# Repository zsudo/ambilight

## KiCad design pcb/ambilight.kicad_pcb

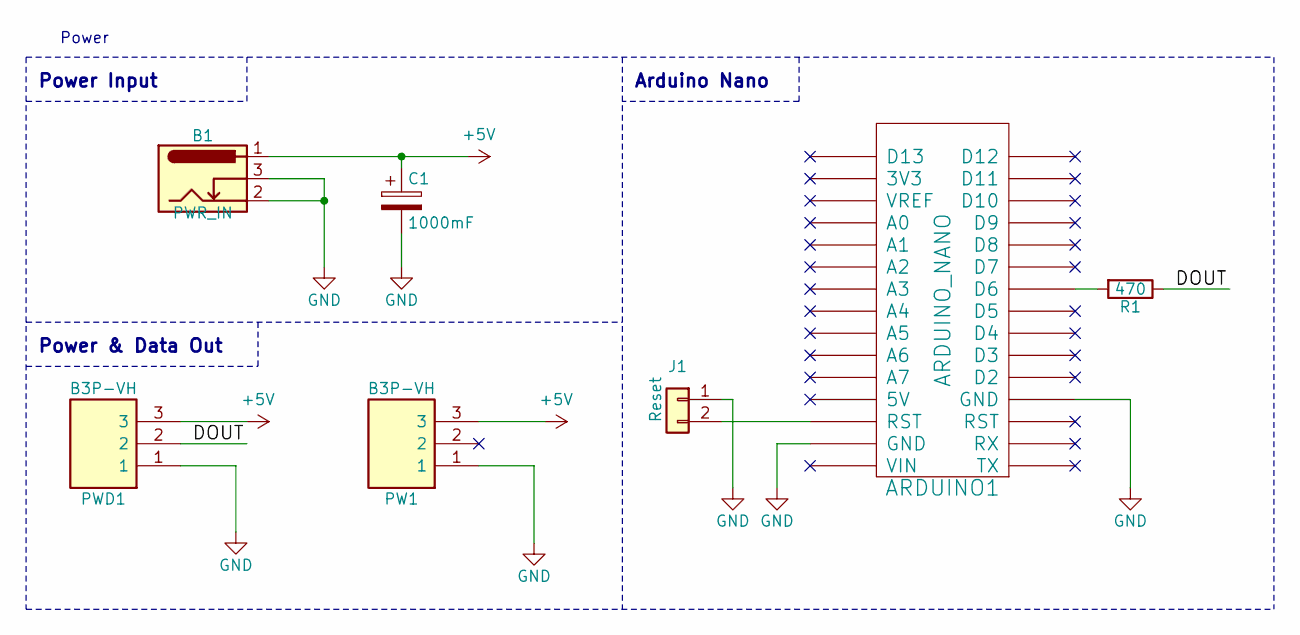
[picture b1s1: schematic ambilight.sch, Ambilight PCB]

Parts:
ARDUINO1: ARDUINO_NANO; Arduino_Nano
B1: PWR_IN; BarrelJack_Horizontal
C1: 1000mF; CP_Radial_D10.0mm_P5.00mm
J1: Reset; PinHeader_1x02_P2.54mm_Vertical
PW1: B3P-VH; SHDR3W114P0X396_1X3_1182X850X940P; Manufacturer_Part_Number B3P-VH
PWD1: B3P-VH; SHDR3W114P0X396_1X3_1182X850X940P; Manufacturer_Part_Number B3P-VH
R1: 470; R_Axial_DIN0411_L9.9mm_D3.6mm_P15.24mm_Horizontal

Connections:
+5V: B1.1, C1.1, PW1.3, PWD1.3
/DOUT: PWD1.2, R1.1
GND: ARDUINO1.4 (GND), ARDUINO1.29 (GND), B1.2, B1.3, C1.2, J1.1, PW1.1, PWD1.1
unnamed: ARDUINO1.9 (D6), R1.2
unnamed: ARDUINO1.28 (RST), J1.2

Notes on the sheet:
Power
Power Input
Power & Data Out
Arduino Nano

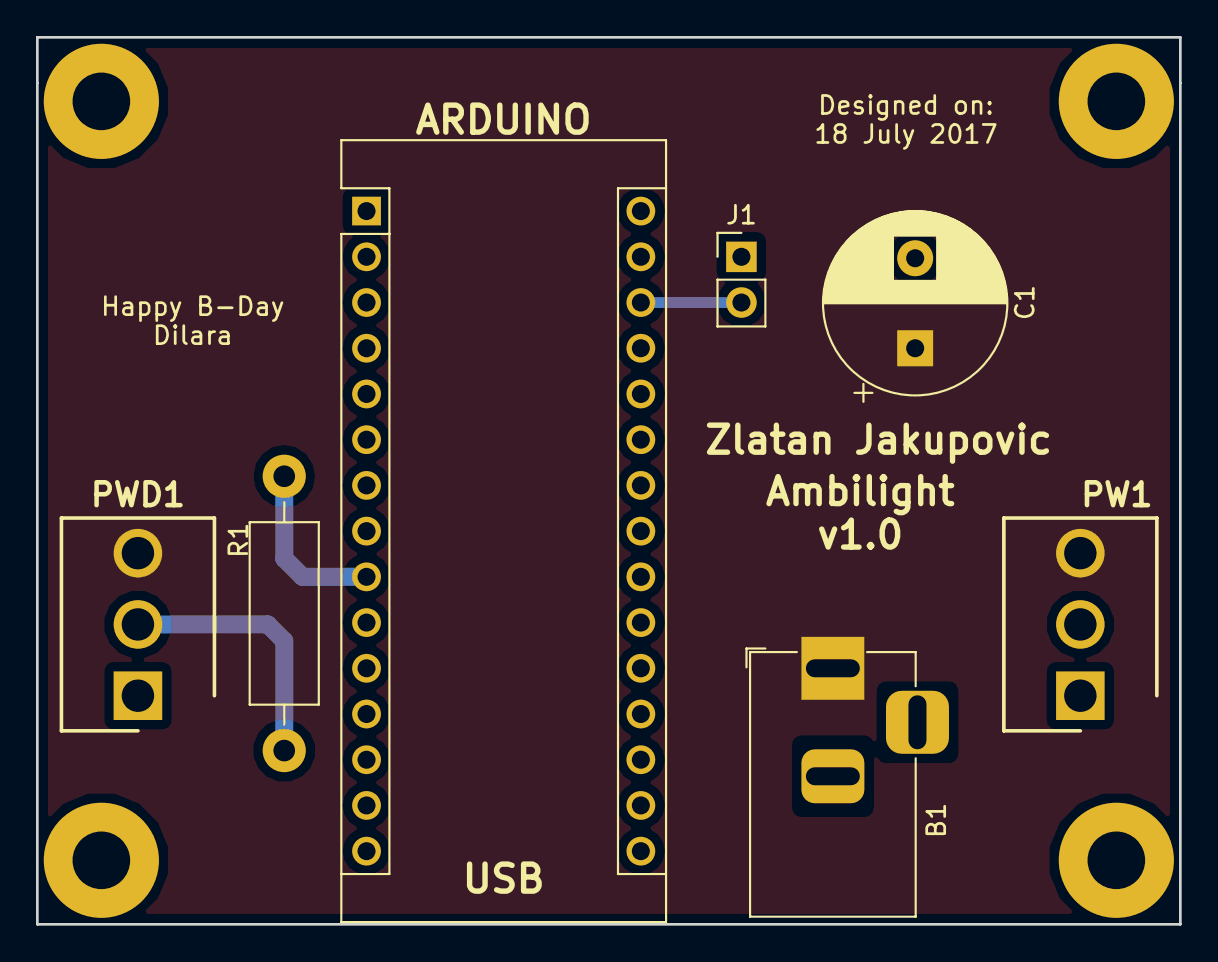
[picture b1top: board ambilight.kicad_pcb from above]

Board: 2 copper layers, 63.5 x 49.3 mm, 11 parts (0 on the bottom side), 5 nets.

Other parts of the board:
M1, M2, M3, M4: MountingHole_3.2mm_M3; MountingHole_3.2mm_M3_Pad

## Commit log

2021-04-02 PCB initial commit
